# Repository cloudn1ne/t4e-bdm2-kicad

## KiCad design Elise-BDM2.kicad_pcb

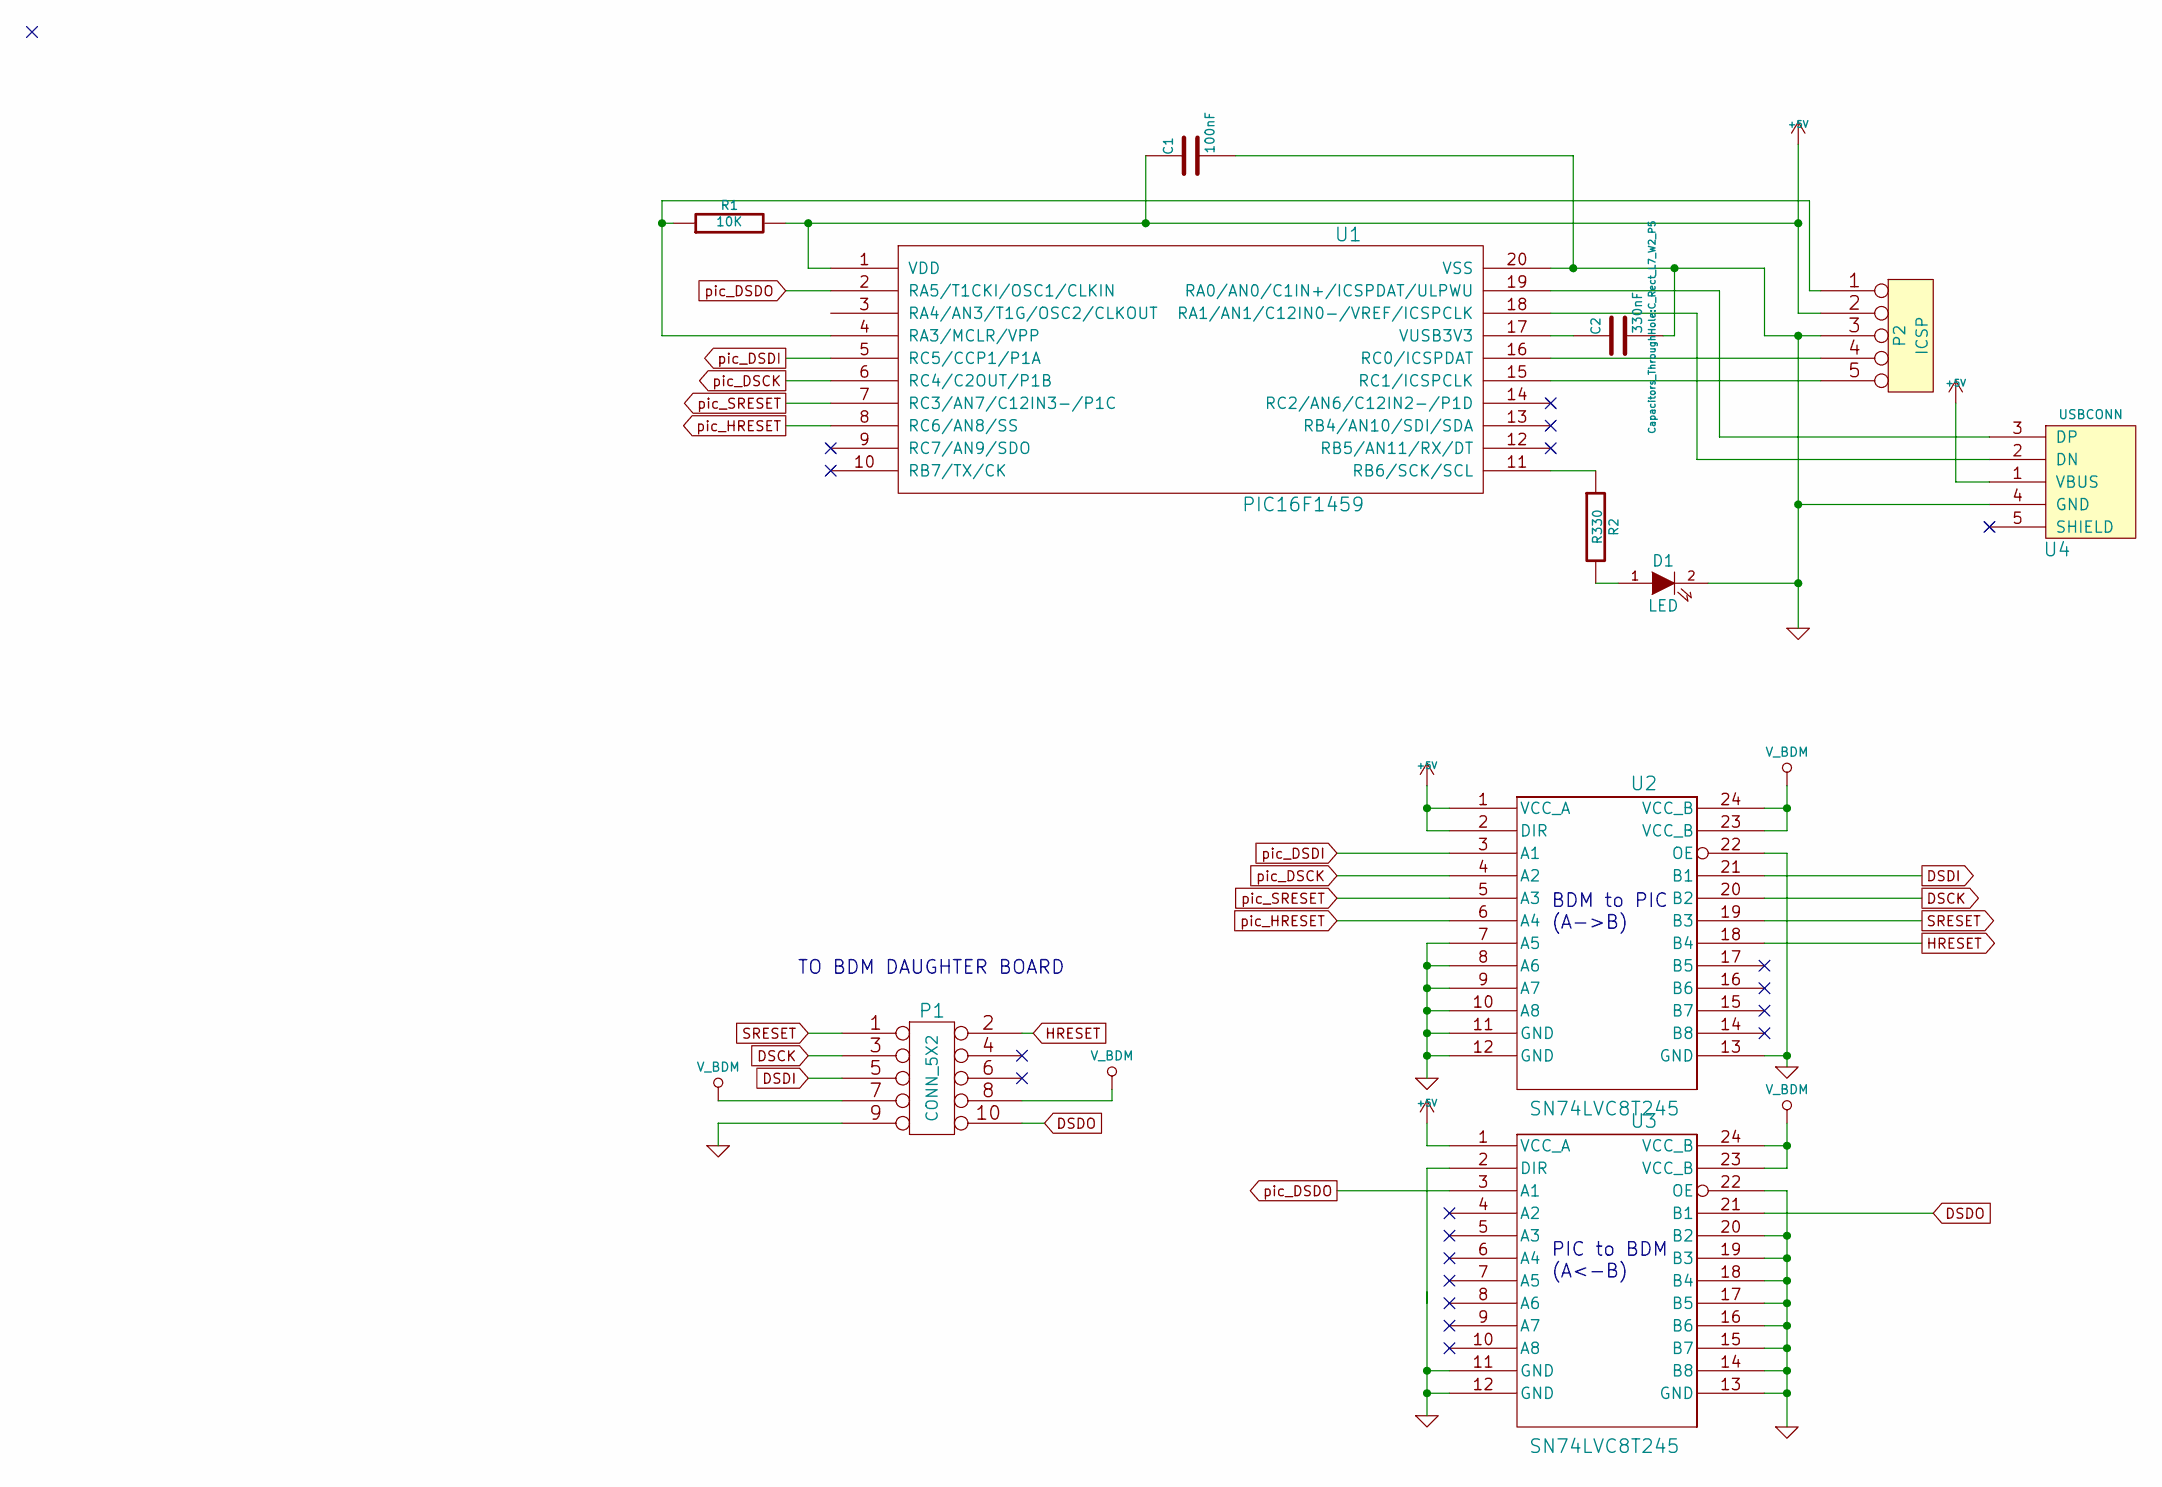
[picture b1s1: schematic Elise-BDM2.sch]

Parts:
C1: 100nF
C2: 330nF; C_Rect_L7_W2_P5
D1: LED
P1: CONN_5X2
P2: ICSP
R1: 10K
R2: R330
U1: PIC16F1459
U2, U3: SN74LVC8T245
U4: USBCONN

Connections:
+5V: C1.1, P2.2, R1.2, U1.1 (VDD), U2.1 (VCC_A), U2.2 (DIR), U3.1 (VCC_A), U4.1 (VBUS)
DSCK: P1.3, U2.20 (B2)
DSDI: P1.5, U2.21 (B1)
DSDO: P1.10, U3.21 (B1)
GND: C1.2, C2.2, D1.2 (K), P1.9, P2.3, U1.20 (VSS), U2.7 (A5), U2.8 (A6), U2.9 (A7), U2.10 (A8), U2.11 (GND), U2.12 (GND), U2.13 (GND), U2.22 (OE), U3.2 (DIR), U3.11 (GND), U3.12 (GND), U3.13 (GND), U3.14 (B8), U3.15 (B7), U3.16 (B6), U3.17 (B5), U3.18 (B4), U3.19 (B3), U3.20 (B2), U3.22 (OE), U4.4 (GND)
HRESET: P1.2, U2.18 (B4)
unnamed: C2.1, U1.17 (VUSB3V3)
unnamed: D1.1 (A), R2.2
unnamed: P2.1, R1.1, U1.4 (RA3/MCLR/VPP)
unnamed: P2.4, U1.16 (RC0/ICSPDAT)
unnamed: P2.5, U1.15 (RC1/ICSPCLK)
unnamed: R2.1, U1.11 (RB6/SCK/SCL)
unnamed: U1.18 (RA1/AN1/C12IN0-/VREF/ICSPCLK), U4.2 (DN)
unnamed: U1.19 (RA0/AN0/C1IN+/ICSPDAT/ULPWU), U4.3 (DP)
SRESET: P1.1, U2.19 (B3)
V_BDM: P1.7, P1.8, U2.23 (VCC_B), U2.24 (VCC_B), U3.23 (VCC_B), U3.24 (VCC_B)
pic_DSCK: U1.6 (RC4/C2OUT/P1B), U2.4 (A2)
pic_DSDI: U1.5 (RC5/CCP1/P1A), U2.3 (A1)
pic_DSDO: U1.2 (RA5/T1CKI/OSC1/CLKIN), U3.3 (A1)
pic_HRESET: U1.8 (RC6/AN8/SS), U2.6 (A4)
pic_SRESET: U1.7 (RC3/AN7/C12IN3-/P1C), U2.5 (A3)

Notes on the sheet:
PIC to BDM (A<-B)
BDM to PIC (A->B)
TO BDM DAUGHTER BOARD

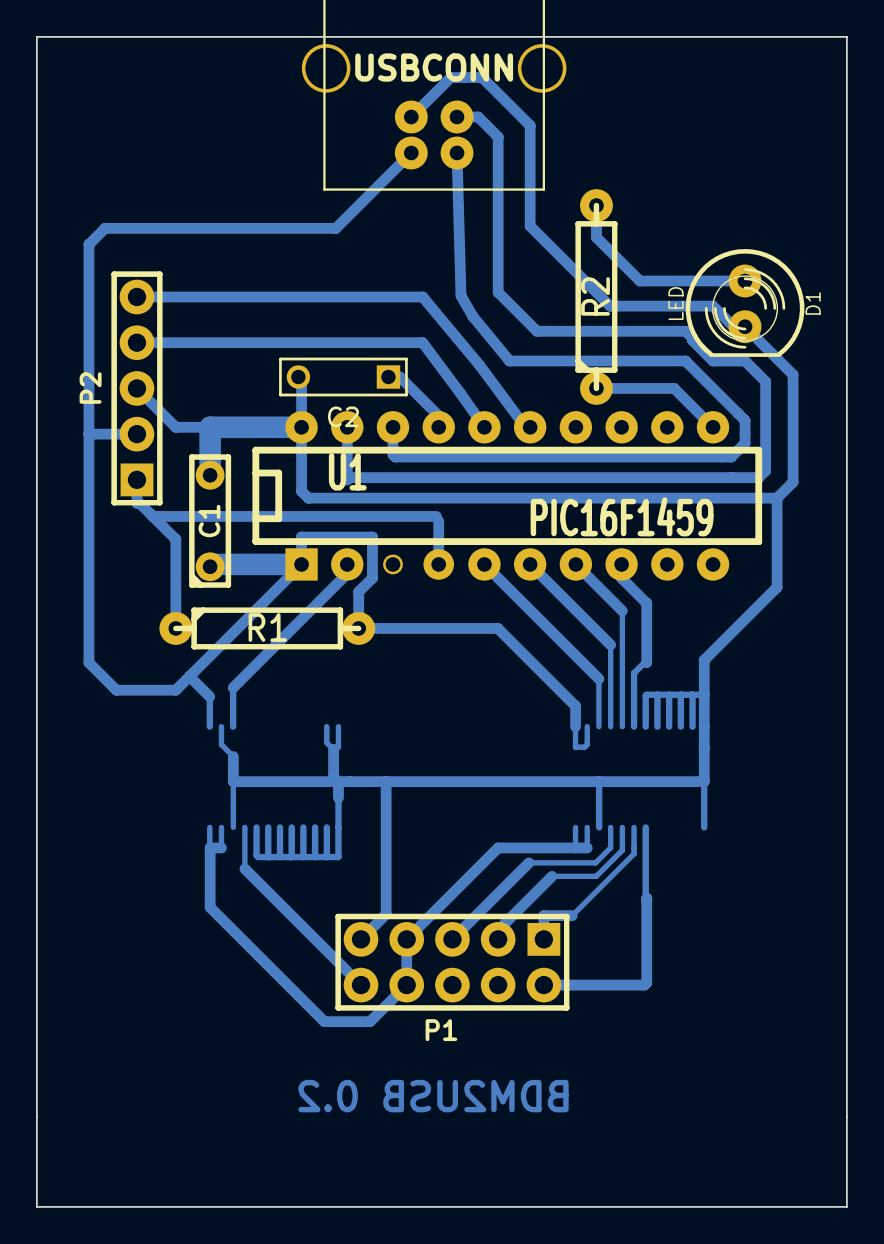
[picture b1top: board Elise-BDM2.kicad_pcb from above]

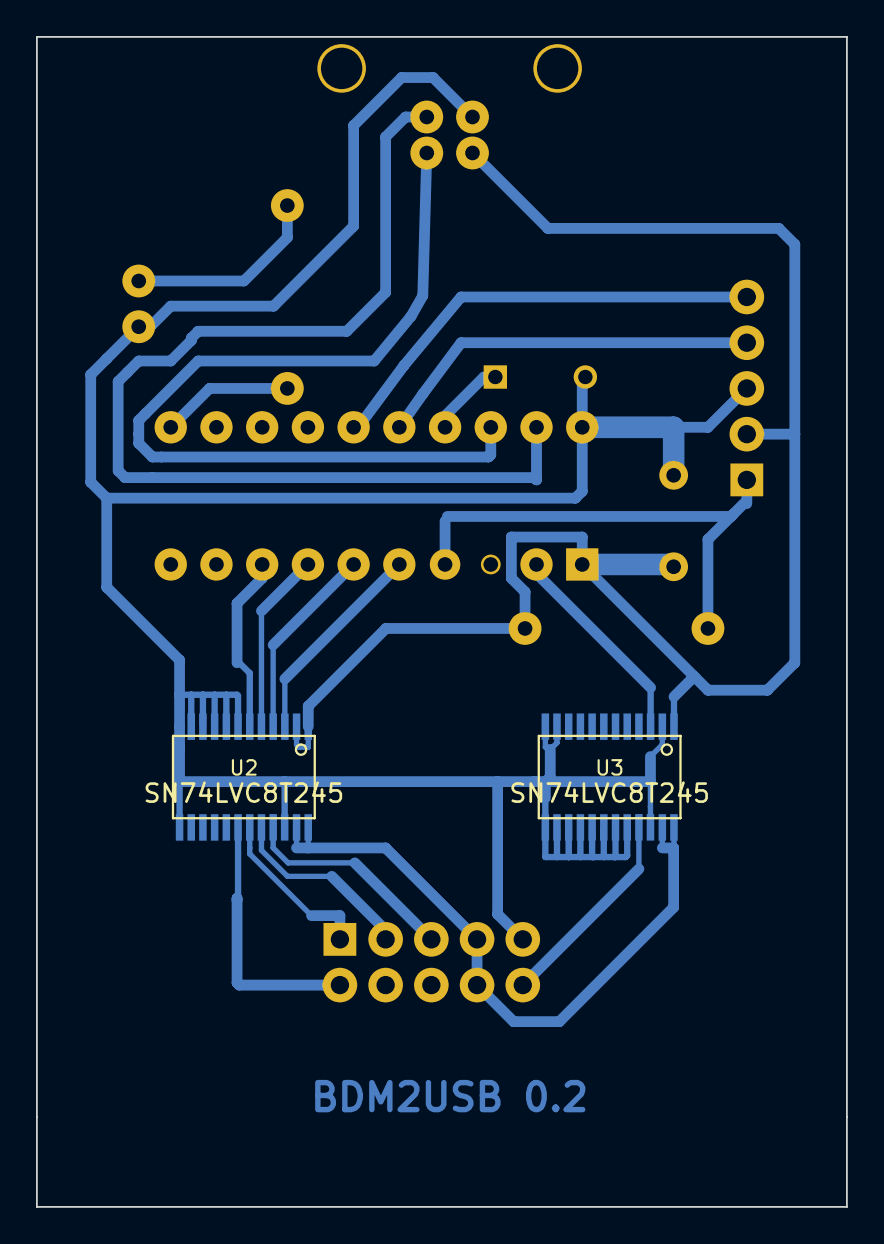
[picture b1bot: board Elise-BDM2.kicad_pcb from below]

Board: 2 copper layers, 45.0 x 65.0 mm, 11 parts (2 on the bottom side), 21 nets.
